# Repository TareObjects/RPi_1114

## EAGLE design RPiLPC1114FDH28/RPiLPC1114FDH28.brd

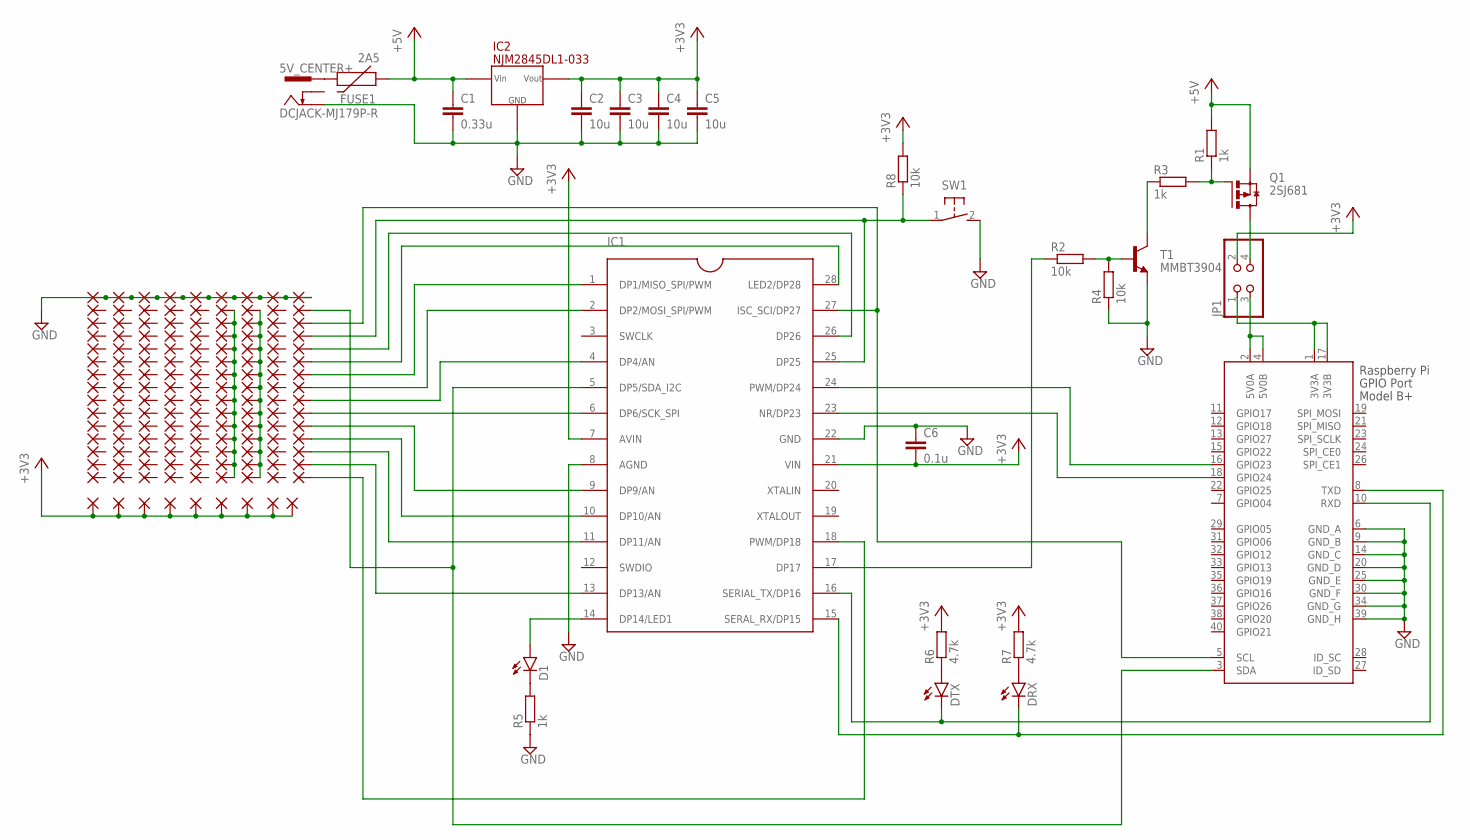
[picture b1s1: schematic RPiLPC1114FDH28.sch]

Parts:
5V_CENTER+: DCJACK-MJ179P-R; MJ-179P-R
C1: 0.33u; C0603
C2, C3, C4, C5: 10u; C0805
C6: 0.1u; C0603
D1: LED0603; LED-0603
DRX: LED0603; LED-0603
DTX: LED0603; LED-0603
FUSE1: 2A5; PTC
IC1: LPC1114DH28; TSSOP28
IC2: NJM2845DL1-033; TO-252-3
JP1: PINHD-2X2; 2X02
PAD1, PAD2, PAD3, PAD4, PAD5, PAD6, PAD7, PAD8, PAD9, PAD10, PAD11, PAD12, PAD13, PAD14, PAD15, PAD16, PAD17, PAD18, PAD19, PAD20, PAD21, PAD22, PAD23, PAD24, PAD25, PAD26, PAD27, PAD28, PAD29, PAD30, PAD31, PAD32, PAD33, PAD34, PAD35, PAD36, PAD37, PAD38, PAD39, PAD40, PAD41, PAD42, PAD43, PAD44, PAD45, PAD46, PAD47, PAD48, PAD49, PAD50, PAD51, PAD53, PAD54, PAD55, PAD56, PAD57, PAD58, PAD59, PAD60, PAD61, PAD62, PAD63, PAD64, PAD65, PAD66, PAD67, PAD69, PAD70, PAD71, PAD72, PAD73, PAD74, PAD75, PAD76, PAD77, PAD78, PAD79, PAD80, PAD81, PAD82, PAD83, PAD100, PAD101, PAD102, PAD103, PAD104, PAD105, PAD106, PAD107, PAD108, PAD109, PAD110, PAD112, PAD113, PAD114, PAD115, PAD117, PAD118, PAD119, PAD120, PAD121, PAD122, PAD123, PAD124, PAD126, PAD127, PAD128, PAD129, PAD130, PAD131, PAD133, PAD134, PAD135, PAD136, PAD137, PAD138, PAD140, PAD141, PAD142, PAD143, PAD144, PAD145, PAD147, PAD148, PAD149, PAD150, PAD151, PAD152: WIREPAD1,6/0,8; 1,6/0,8
PAD-3V3: WIREPAD1,6/0,8; 1,6/0,8
PAD-DP1, PAD-DP2, PAD-DP4, PAD-DP5/SDA, PAD-DP6, PAD-DP9, PAD-DP10, PAD-DP11, PAD-DP13, PAD-DP18, PAD-DP25, PAD-DP26, PAD-DP27/SCL, PAD-DP28: WIREPAD1,6/0,8; 1,6/0,8
PAD_GND: WIREPAD1,6/0,8; 1,6/0,8
Q1: 2SJ681; 2-7J2B(TOSHIBA)
R1, R3, R5: 1k; R0603
R2, R4, R8: 10k; R0603
R6, R7: 4.7k; R0603
SW1: SWITCH-TACTILESW; SWITCH-TACTILE
T1: MMBT3904; SOT23-3
X1: RASPI_GPIO_B+#_PIN; RASPI_GPIO_B+_PIN

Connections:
+3V3: C2.1, C3.1, C4.1, C5.1, C6.2, IC1.7 (AVIN), IC1.21 (VIN), IC2.VOUT, JP1.2, PAD117.1, PAD118.1, PAD119.1, PAD120.1, PAD121.1, PAD122.1, PAD123.1, PAD124.1, PAD-3V3.1, R6.2, R7.2, R8.2
+5V: C1.1, FUSE1.P$1 (1), IC2.VIN, Q1.P$3 (S), R1.2
GND: 5V_CENTER+.2, C1.2, C2.2, C3.2, C4.2, C5.2, C6.1, IC1.8 (AGND), IC1.22 (GND), IC2.GND, PAD1.1, PAD10.1, PAD19.1, PAD28.1, PAD37.1, PAD53.1, PAD69.1, PAD100.1, PAD_GND.1, R4.1, R5.1, SW1.2, T1.2 (E), X1.6 (GND_A), X1.9 (GND_B), X1.14 (GND_C), X1.20 (GND_D), X1.25 (GND_E), X1.30 (GND_F), X1.34 (GND_G), X1.39 (GND_H)
unnamed: DRX.C, IC1.15 (SERAL_RX/DP15), X1.8 (TXD)
unnamed: IC1.2 (DP2/MOSI_SPI/PWM), PAD-DP2.1
unnamed: IC1.5 (DP5/SDA_I2C), PAD-DP5/SDA.1, X1.3 (SDA)
unnamed: IC1.27 (ISC_SCI/DP27), PAD-DP27/SCL.1, X1.5 (SCL)
unnamed: R2.2, R4.2, T1.1 (B)
unnamed: R3.1, T1.3 (C)
unnamed: Q1.P$1 (G), R1.1, R3.2
unnamed: JP1.3, X1.2 (5V0A), X1.4 (5V0B)
unnamed: 5V_CENTER+.1, FUSE1.P$2 (2)
unnamed: IC1.23 (NR/DP23), X1.18 (GPIO24)
unnamed: IC1.24 (PWM/DP24), X1.16 (GPIO23)
unnamed: IC1.17 (DP17), R2.1
unnamed: D1.C, R5.2
unnamed: D1.A, IC1.14 (DP14/LED1)
unnamed: DTX.A, R6.1
unnamed: DRX.A, R7.1
unnamed: DTX.C, IC1.16 (SERIAL_TX/DP16), X1.10 (RXD)
unnamed: IC1.1 (DP1/MISO_SPI/PWM), PAD-DP1.1
unnamed: IC1.4 (DP4/AN), PAD-DP4.1
unnamed: IC1.6 (DP6/SCK_SPI), PAD-DP6.1
unnamed: IC1.13 (DP13/AN), PAD-DP13.1
unnamed: IC1.11 (DP11/AN), PAD-DP11.1
unnamed: IC1.10 (DP10/AN), PAD-DP10.1
unnamed: IC1.9 (DP9/AN), PAD-DP9.1
unnamed: IC1.18 (PWM/DP18), PAD-DP18.1
unnamed: IC1.28 (LED2/DP28), PAD-DP28.1
unnamed: IC1.26 (DP26), PAD-DP26.1
unnamed: IC1.25 (DP25), PAD-DP25.1, R8.1, SW1.1
unnamed: JP1.1, X1.1 (3V3A), X1.17 (3V3B)
unnamed: JP1.4, Q1.P$2 (D)
unnamed: PAD54.1, PAD55.1, PAD56.1, PAD57.1, PAD58.1, PAD59.1, PAD60.1, PAD61.1, PAD62.1, PAD63.1, PAD64.1, PAD65.1, PAD66.1, PAD67.1
unnamed: PAD70.1, PAD71.1, PAD72.1, PAD73.1, PAD74.1, PAD75.1, PAD76.1, PAD77.1, PAD78.1, PAD79.1, PAD80.1, PAD81.1, PAD82.1, PAD83.1

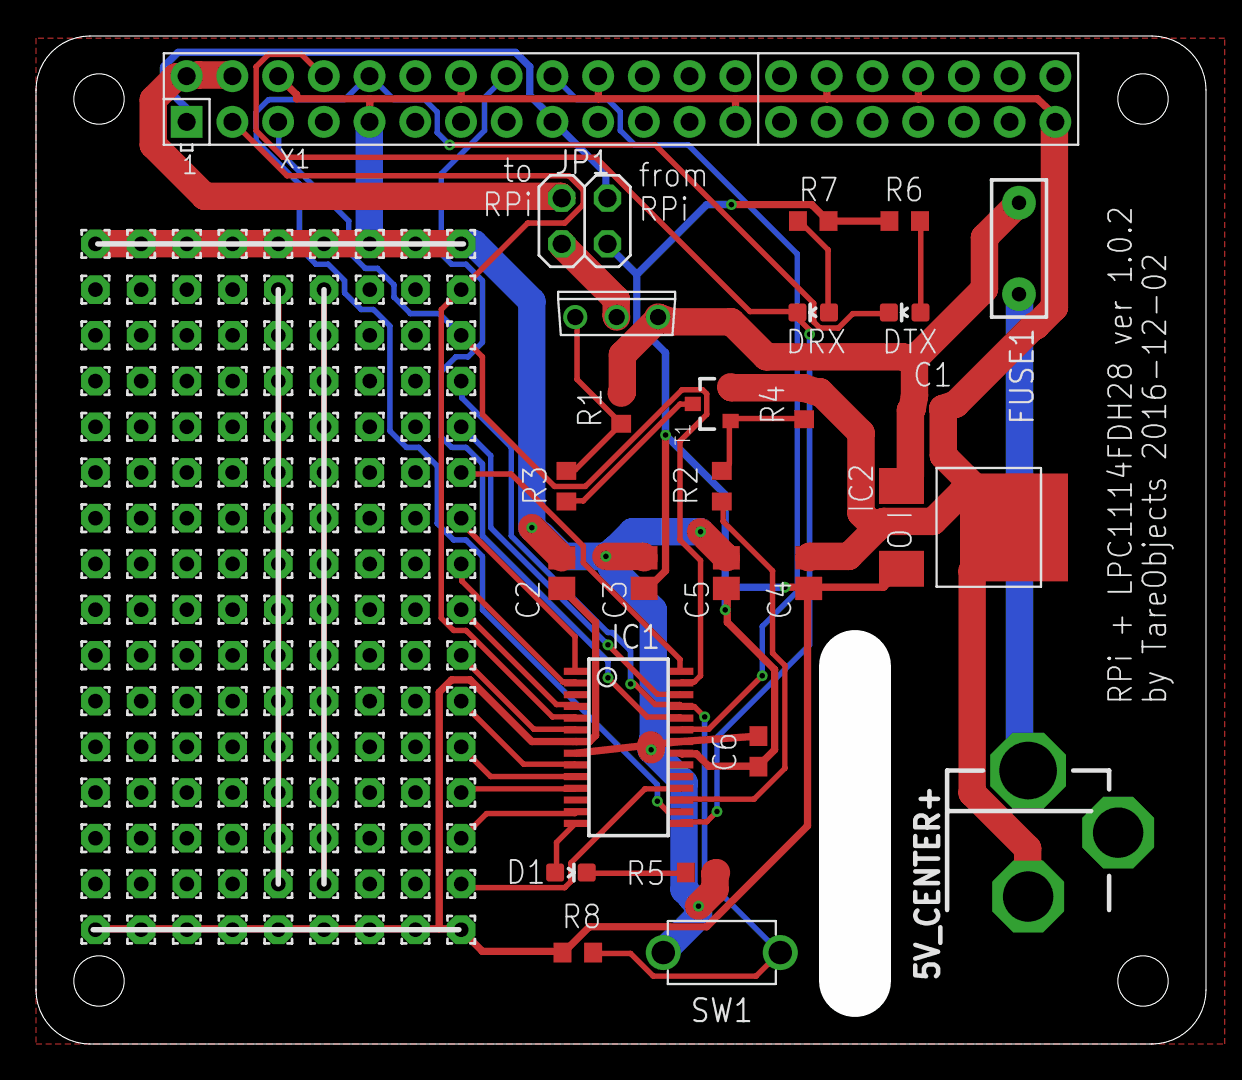
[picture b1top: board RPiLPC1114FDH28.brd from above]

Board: 2 copper layers, 65.0 x 56.0 mm, 170 parts (0 on the bottom side), 35 nets.

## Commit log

2017-01-03 ここはバイナリダウンロード用 ソースなどはこちらに公開しています https://developer.mbed.org/users/TareObjects/code/RPi_1114/
2017-01-03 回路図とパターン
2017-01-04 timer on / timer offコマンドが正常に機能しないバグをfix sw1で電源を強制的にon / offする機能を追加
2017-01-13 アナログポート読み込み、アナログデータバッファリング、デジタルポート入出力など対応。
2017-01-16 ver 1.0 : 全コマンド実装・動作確認
2017-01-17 ファームウェアバージョン表示機能を追加 0x30アナログ取得コマンドのch指定エラーバグを修正

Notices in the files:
parts and their libraries:
SparkFun-LED: Licensing: Creative Commons ShareAlike 4.0 International - https://creativecommons.org/licenses/by-sa/4.0
